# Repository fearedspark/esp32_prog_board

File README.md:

# ESP32 Programming/Debugging Board

This project is a simple board to program and debug ESP32 chip using a USB-C port.

The core is a CP2104 USB-to-Serial converter and it uses the `RTS` and `DTS` signals to reset the MCU in boot mode for programming.

The programming post is a 6-pins JST PH SMT connector, with the following mapping:

|Pin #|Signal Name|Note                                            |
|:---:|-----------|------------------------------------------------|
|1    |+3.3V      |                                                |
|2    |GND        |                                                |
|3    |TX         |From host to target                             |
|4    |RX         |From target to host                             |
|5    |RESET      |The board has a button shorting this line to GND|
|6    |BOOT0      |Should be connected directly to GPIO0           |

## Bill of Material

You can find the BOM on Octopart via this [link](https://octopart.com/bom-tool/CL9CJzFa).

|Reference Designator|Manufacturer    |Product Number       |Description                     |Quantity|Value|Tolerance|Rating|Package     |
|--------------------|----------------|---------------------|--------------------------------|--------|-----|---------|------|------------|
|U1                  |Diodes Inc.     |AP2112K-3.3          |3.3V 600mA LDO w/ EN            |1       |     |         |      |SOT25       |
|U2                  |Silicon Labs    |CP2104               |USB-to-UART Bridge              |1       |     |         |      |QFN-24      |
|ESD1                |ON Semiconductor|ESD5B5.0ST1G         |TVS Diode 5V                    |1       |     |         |      |SOD523      |
|ESD2                |LittelFuse      |SP3401               |TVS Diode Arrays for USB        |1       |     |         |      |JEDEC MO-229|
|D1                  |Würth Elektronik|150060RS75000        |Red LED                         |1       |     |         |      |0603        |
|D2                  |Würth Elektronik|150060GS75000        |Green LED                       |1       |     |         |      |0603        |
|D3                  |Würth Elektronik|150060BS75000        |Blue LED                        |1       |     |         |      |0603        |
|Q1                  |Diodes Inc.     |MMDT2222A            |Dual Small Signal NPN Transistor|1       |     |         |      |SOT363      |
|C1, C2, C4          |                |                     |10µF, 10V SMT Ceramic Capacitor |3       |10µF |≤±20%    |≥10V  |0603        |
|C3                  |                |                     |1µF, 10V SMT Ceramic Capacitor  |1       |1µF  |≤±20%    |≥10V  |0603        |
|C5\*                |                |                     |4.7µF, 10V SMT Ceramic Capacitor|1       |4.7µF|≤±20%    |≥10V  |0603        |
|R1, R2              |                |                     |5.1kΩ SMT Resistor              |2       |5.1kΩ|≤±1%     |      |0603        |
|R3                  |                |                     |100kΩ SMT Resistor              |1       |100kΩ|≤±5%     |      |0603        |
|R4, R5, R6          |                |                     |10kΩ SMT Resistor               |3       |10kΩ |≤±5%     |      |0603        |
|R7                  |                |                     |330Ω                            |1       |330Ω |≤±5%     |      |0603        |
|R8                  |                |                     |120Ω                            |1       |120Ω |≤±5%     |      |0603        |
|R9                  |                |                     |91Ω                             |1       |91Ω  |≤±5%     |      |0603        |
|J1                  |Molex           |105450-0101          |USB-C SMT Connector             |1       |     |         |      |            |
|J2                  |JST Inc.        |S6B-PH-SM4-TB(LF)(SN)|6-Pins SMT JST PH Connector     |1       |     |         |      |            |

> Notes:
> - \*`C5` is only required to modify the device OTP memory. It can be ignored.
> - Red LED is for power, Blue LED is for host RX, Green LED is for host TX.

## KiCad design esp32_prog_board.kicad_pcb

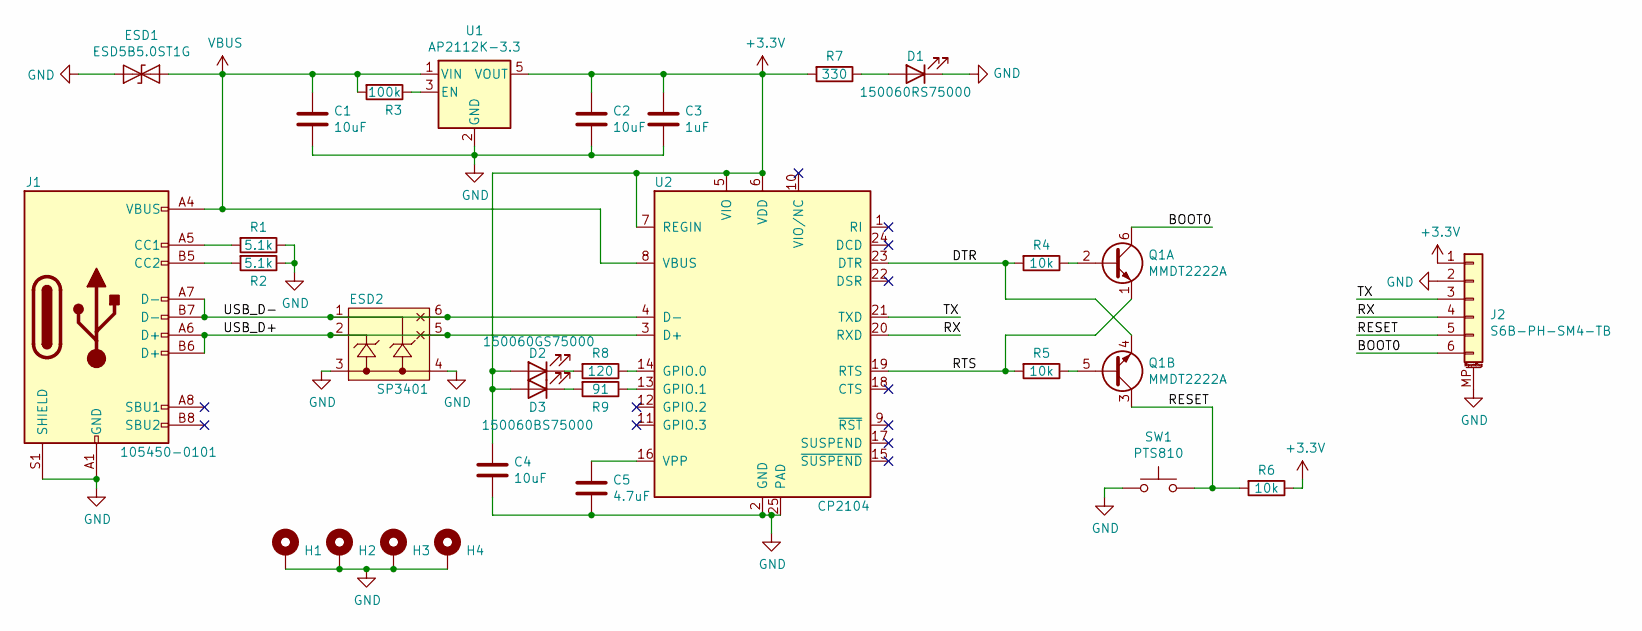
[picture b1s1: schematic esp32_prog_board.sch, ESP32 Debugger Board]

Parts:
C1, C2, C4: 10uF; R_0603_1608Metric
C3: 1uF; R_0603_1608Metric
C5: 4.7uF; R_0603_1608Metric
D1: 150060RS75000; LED_0603_1608Metric
D2: 150060GS75000; LED_0603_1608Metric
D3: 150060BS75000; LED_0603_1608Metric
ESD1: ESD5B5.0ST1G; D_SOD-523
ESD2: SP3401
H1, H2, H3, H4: MountingHole_Pad; MountingHole_2.7mm_M2.5_Pad
J1: 105450-0101
J2: S6B-PH-SM4-TB; JST_PH_S6B-PH-SM4-TB_1x06-1MP_P2.00mm_Horizontal
Q1: MMDT2222A; SOT-363_SC-70-6
R1, R2: 5.1k; R_0603_1608Metric
R3: 100k; R_0603_1608Metric
R4, R5, R6: 10k; R_0603_1608Metric
R7: 330; R_0603_1608Metric
R8: 120; R_0603_1608Metric
R9: 91; R_0603_1608Metric
SW1: PTS810; SW_SPST_PTS810
U1: AP2112K-3.3; SOT-23-5
U2: CP2104; QFN-24-1EP_4x4mm_P0.5mm_EP2.6x2.6mm

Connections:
+3V3: C2.1, C3.1, C4.1, D2.2 (A), D3.2 (A), J2.1, R6.1, R7.2, U1.5 (VOUT), U2.5 (VIO), U2.6 (VDD), U2.7 (REGIN)
/BOOT0: J2.6, Q1.6 (C1)
/DTR: Q1.4 (E2), R4.2, U2.23 (DTR)
/RESET: J2.5, Q1.3 (C2), R6.2, SW1.2
/RTS: Q1.1 (E1), R5.2, U2.19 (RTS)
/RX: J2.4, U2.20 (RXD)
/TX: J2.3, U2.21 (TXD)
/USB_D+: ESD2.2, ESD2.5, J1.A6 (D+), J1.B6 (D+), U2.3 (D+)
/USB_D-: ESD2.1, ESD2.6, J1.A7 (D-), J1.B7 (D-), U2.4 (D-)
GND: C1.2, C2.2, C3.2, C4.2, C5.2, D1.1 (K), ESD1.1 (A1), ESD2.3, ESD2.4, H1.1, H2.1, H3.1, H4.1, J1.A1 (GND), J1.A12 (GND), J1.B1 (GND), J1.B12 (GND), J1.S1 (SHIELD), J2.2, J2.MP (MountPin), R1.1, R2.1, SW1.1, U1.2 (GND), U2.2 (GND), U2.25 (PAD)
unnamed: C5.1, U2.16 (VPP)
unnamed: D1.2 (A), R7.1
unnamed: D2.1 (K), R8.2
unnamed: D3.1 (K), R9.2
unnamed: J1.A5 (CC1), R1.2
unnamed: J1.B5 (CC2), R2.2
unnamed: Q1.2 (B1), R4.1
unnamed: Q1.5 (B2), R5.1
unnamed: R3.1, U1.3 (EN)
unnamed: R8.1, U2.14 (GPIO.0)
unnamed: R9.1, U2.13 (GPIO.1)
VBUS: C1.1, ESD1.2 (A2), J1.A4 (VBUS), J1.A9 (VBUS), J1.B4 (VBUS), J1.B9 (VBUS), R3.2, U1.1 (VIN), U2.8 (VBUS)

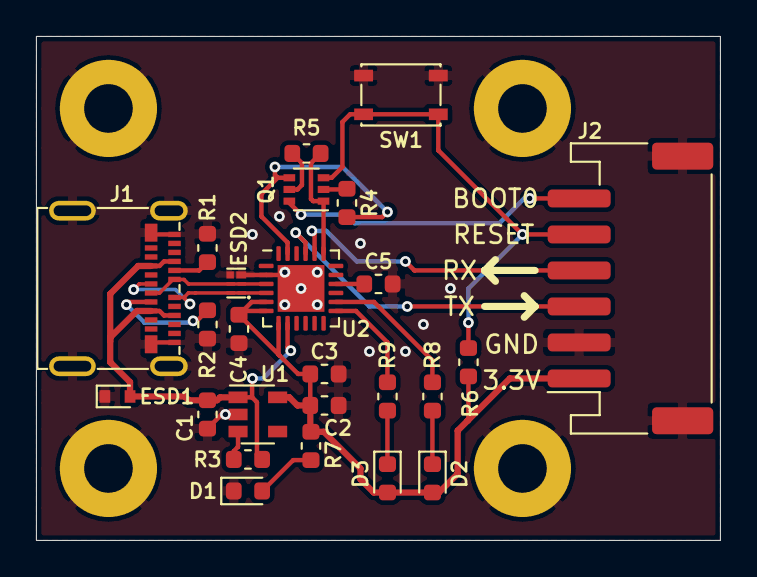
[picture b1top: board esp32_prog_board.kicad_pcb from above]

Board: 2 copper layers, 38.0 x 28.0 mm, 29 parts (0 on the bottom side), 22 nets.

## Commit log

2020-08-04 Created project
2020-08-04 Added LittelFuse SP3401 component
2020-08-04 Added Molex USB-C connector footprint
2020-08-04 Linked project libraries
2020-08-05 Completed schematic
2020-08-05 Updated BOM
2020-08-05 Added VBUS ESD, and TX/RX/PWR LEDs
2020-08-06 Completed routing
2020-08-06 Added Octopart BOM link
